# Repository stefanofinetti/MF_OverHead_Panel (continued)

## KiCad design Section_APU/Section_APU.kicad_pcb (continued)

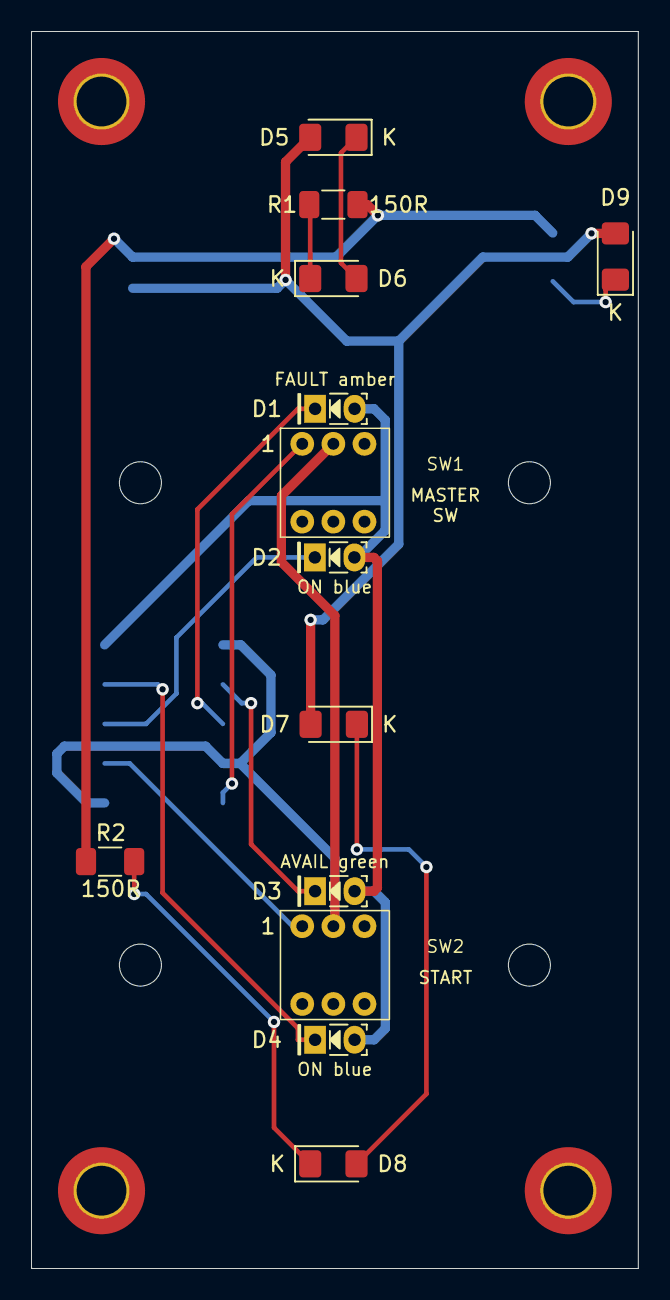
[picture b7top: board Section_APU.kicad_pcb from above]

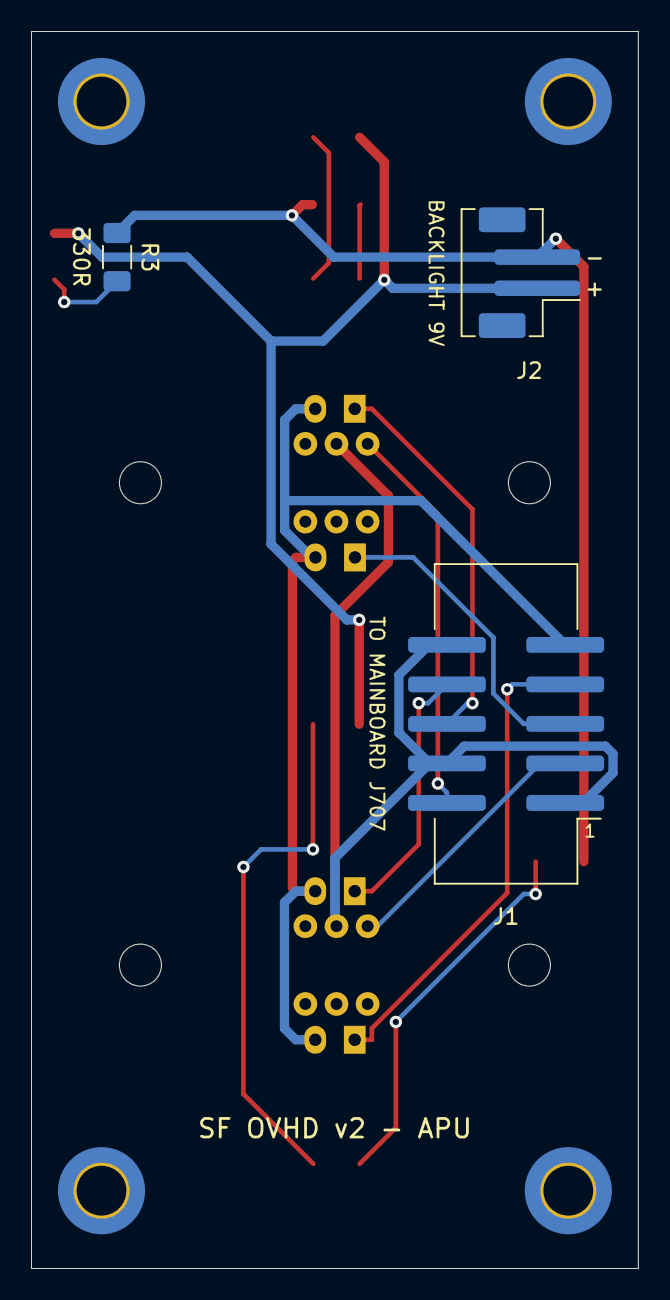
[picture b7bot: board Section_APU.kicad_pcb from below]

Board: 2 copper layers, 39.0 x 79.5 mm, 24 parts (3 on the bottom side), 15 nets.

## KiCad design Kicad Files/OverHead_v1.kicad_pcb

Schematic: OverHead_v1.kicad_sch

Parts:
C1, C2, C3, C4, C7: 100nF; C_1206_3216Metric_Pad1.33x1.80mm_HandSolder
C5: 10uF; C_Elec_4x5.4
C6, C8, C9: 22pF; C_1206_3216Metric_Pad1.33x1.80mm_HandSolder
R1: 10K; R_1206_3216Metric_Pad1.30x1.75mm_HandSolder
U1: ATMega2560; TQFP100-0.5-14X14MM
XT16MHz1: 16MHz; Crystal_SMD_EuroQuartz_MQ-4Pin_7.0x5.0mm_HandSoldering

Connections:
ADR_1_ATT: U1.63 (PJ0); also elsewhere on the board
ADR_1_NAV: U1.64 (PJ1); also elsewhere on the board
ADR_1_OFF: U1.35 (PL0); also elsewhere on the board
ADR_2_ATT: U1.89 (PK0); also elsewhere on the board
ADR_2_NAV: U1.88 (PK1); also elsewhere on the board
ADR_2_OFF: U1.36 (PL1); also elsewhere on the board
ADR_3_ATT: U1.87 (PK2); also elsewhere on the board
ADR_3_NAV: U1.86 (PK3); also elsewhere on the board
ADR_3_OFF: U1.37 (PL2); also elsewhere on the board
ANTI_ICE_ENG1_SW: U1.96 (PF1); also elsewhere on the board
ANTI_ICE_ENG2_SW: U1.95 (PF2); also elsewhere on the board
ANTI_ICE_WING_SW: U1.97 (PF0); also elsewhere on the board
APU_BLEED_SW: U1.90 (PF7); also elsewhere on the board
APU_MASTER_SW: U1.72 (PA6); also elsewhere on the board
APU_START_SW: U1.71 (PA7); also elsewhere on the board
BEACON_ON: U1.58 (PC5); also elsewhere on the board
CLK1: U1.76 (PA2); also elsewhere on the board
CLK2: U1.74 (PA4); also elsewhere on the board
CTR_TK_PUMP_1_SW: U1.17 (PH5); also elsewhere on the board
CTR_TK_PUMP_2_SW: U1.18 (PH6); also elsewhere on the board
DIN1: U1.78 (PA0); also elsewhere on the board
DIN2: U1.75 (PA3); also elsewhere on the board
ELEC_BATT_1_SW: U1.84 (PK5); also elsewhere on the board
ELEC_BATT_2_SW: U1.83 (PK6); also elsewhere on the board
EMERG_OFF: U1.7 (PE5); also elsewhere on the board
EMERG_ON: U1.6 (PE4); also elsewhere on the board
EXT_PWR_SW: U1.70 (PG2); also elsewhere on the board
GND: C1.2, C2.2, C3.2, C4.2, C5.2, C6.2, C7.2, C8.2, C9.2, U1.11 (GND), U1.32 (GND), U1.62 (GND), U1.81 (GND), U1.99 (GND), XT16MHz1.2, XT16MHz1.4; also elsewhere on the board
GND_CTL_SW: U1.82 (PK7); also elsewhere on the board
GPWS_FLAPS3_SW: U1.91 (PF6); also elsewhere on the board
GPWS_GS_SW: U1.92 (PF5); also elsewhere on the board
GPWS_SYS_SW: U1.93 (PF4); also elsewhere on the board
GPWS_TERR_SW: U1.94 (PF3); also elsewhere on the board
LCH1: U1.77 (PA1); also elsewhere on the board
LCH2: U1.73 (PA5); also elsewhere on the board
LT_TK_PUMP_1_SW: U1.12 (PH0); also elsewhere on the board
LT_TK_PUMP_2_SW: U1.13 (PH1); also elsewhere on the board
L_LDG_LIGHT_ON: U1.23 (PB4); also elsewhere on the board
L_LDG_LIGHT_RETR: U1.24 (PB5); also elsewhere on the board
MISO: U1.22 (PB3); also elsewhere on the board
MOSI: U1.21 (PB2); also elsewhere on the board
NAV_1: U1.56 (PC3); also elsewhere on the board
NAV_1_OFF: U1.55 (PC2); also elsewhere on the board
NOSE_OFF: U1.54 (PC1); also elsewhere on the board
NOSE_TO: U1.53 (PC0); also elsewhere on the board
NOSMOKING_ON: U1.50 (PD7); also elsewhere on the board
unnamed: C7.1, U1.98 (AREF)
unnamed: C9.1, U1.34 (XTAL1), XT16MHz1.1
unnamed: C8.1, U1.33 (XTAL2), XT16MHz1.3
OXY_CREW_SUPPLY_SW: U1.85 (PK4); also elsewhere on the board
PACK1_SW: U1.51 (PG0); also elsewhere on the board
PACK2_SW: U1.52 (PG1); also elsewhere on the board
RESET: C6.1, R1.2, U1.30 (~RESET); also elsewhere on the board
RT_TK_PUMP_1_SW: U1.15 (PH3); also elsewhere on the board
RT_TK_PUMP_2_SW: U1.16 (PH4); also elsewhere on the board
RWY_TURN_ON: U1.60 (PC7); also elsewhere on the board
RXD: U1.2 (PE0); also elsewhere on the board
R_LDG_LIGHT_ON: U1.25 (PB6); also elsewhere on the board
R_LDG_LIGHT_RETR: U1.26 (PB7); also elsewhere on the board
SCK: U1.20 (PB1); also elsewhere on the board
SCL: U1.43 (PD0); also elsewhere on the board
SDA: U1.44 (PD1); also elsewhere on the board
SEATBELTS_ON: U1.45 (PD2); also elsewhere on the board
STROBE_ON: U1.59 (PC6); also elsewhere on the board
TXD: U1.3 (PE1); also elsewhere on the board
VIN: C1.1, C2.1, C3.1, C4.1, C5.1, R1.1, U1.10 (VCC), U1.31 (VCC), U1.61 (VCC), U1.80 (VCC), U1.100 (AVCC); also elsewhere on the board
WING_ON: U1.57 (PC4); also elsewhere on the board
XFEED_SW: U1.1 (PG5); also elsewhere on the board

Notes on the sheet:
DM13A Drivers

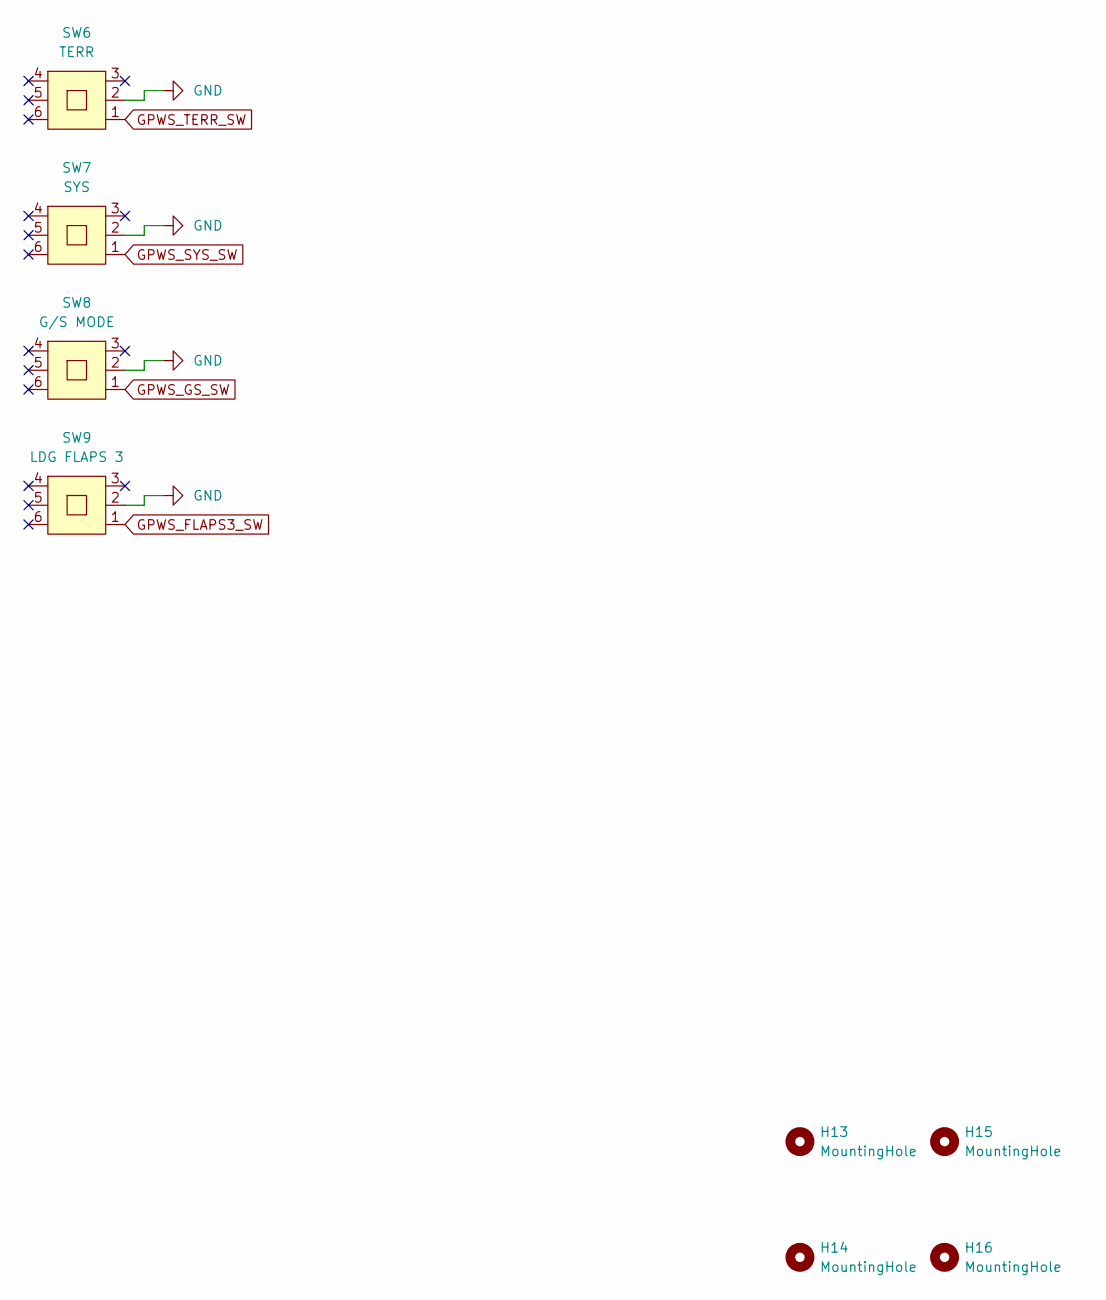
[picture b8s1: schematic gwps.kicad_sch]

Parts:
H13, H14, H15, H16: MountingHole; MountingHole_3.2mm_M3_DIN965_Pad_TopBottom
SW6: TERR; G-Switch PS-7054DVB-6PN
SW7: SYS; G-Switch PS-7054DVB-6PN
SW8: G/S MODE; G-Switch PS-7054DVB-6PN
SW9: LDG FLAPS 3; G-Switch PS-7054DVB-6PN

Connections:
GND: SW6.2, SW7.2, SW8.2, SW9.2; also elsewhere on the board
GPWS_FLAPS3_SW: SW9.1; also elsewhere on the board
GPWS_GS_SW: SW8.1; also elsewhere on the board
GPWS_SYS_SW: SW7.1; also elsewhere on the board
GPWS_TERR_SW: SW6.1; also elsewhere on the board

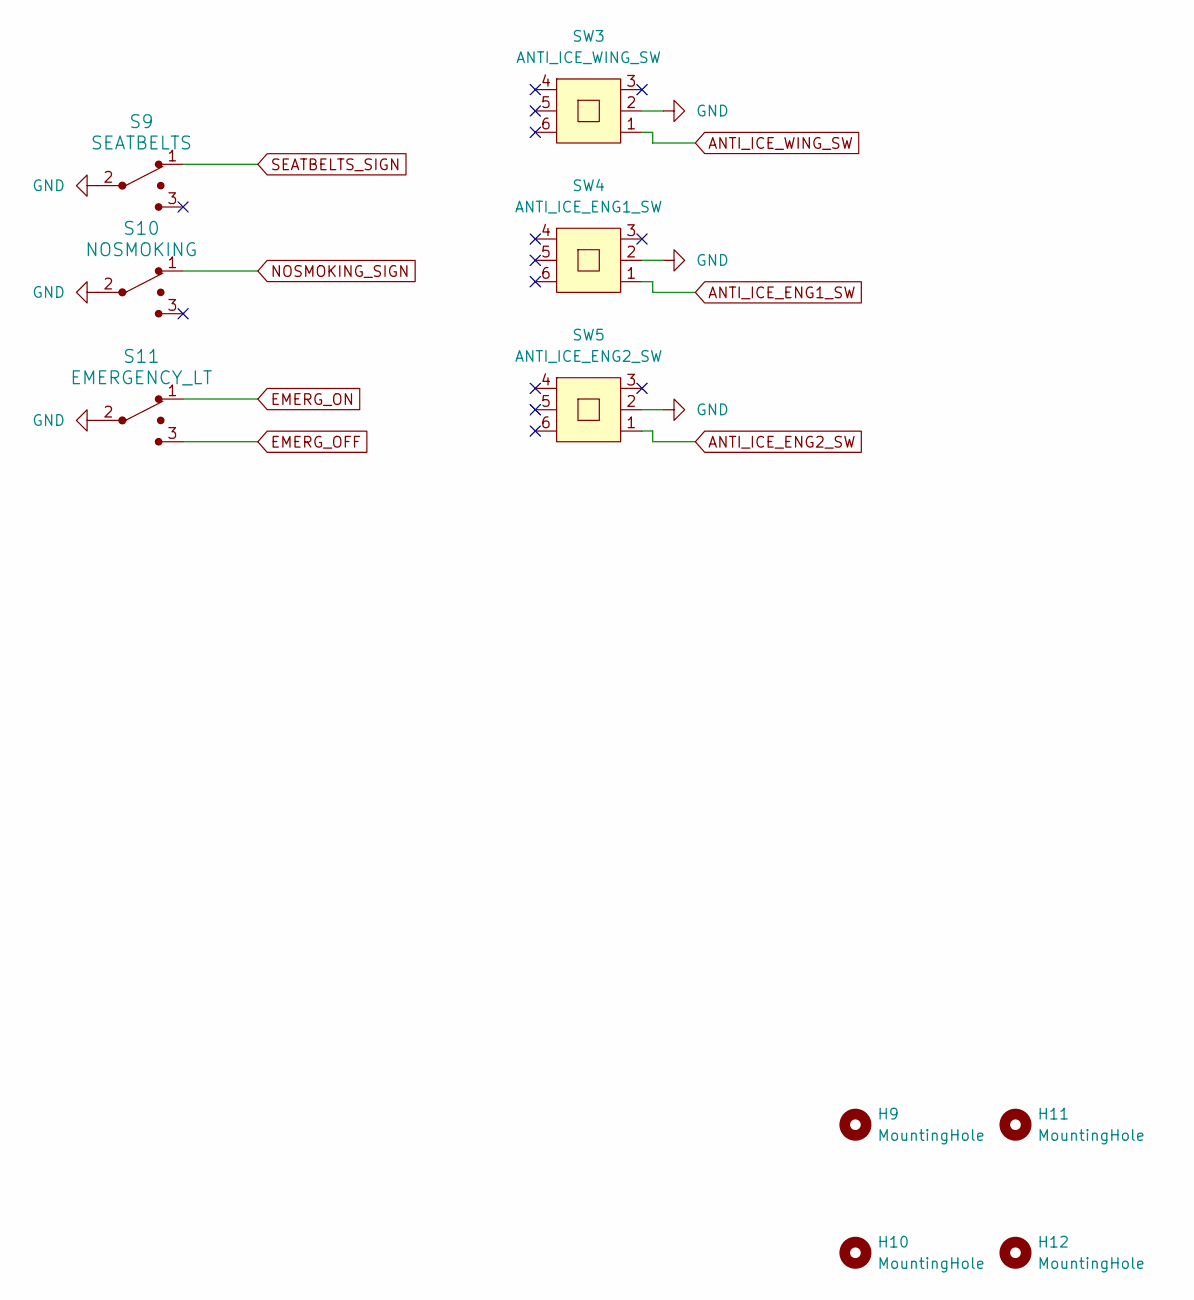
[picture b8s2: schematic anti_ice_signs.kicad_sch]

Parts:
H9, H10, H11, H12: MountingHole; MountingHole_3.2mm_M3_DIN965_Pad_TopBottom
S9: SEATBELTS; Toggle_Switch_100SP1T1B4M2QE; MPN 100SP1T1B4M2QE; Digi-Key_PN EG2355-ND
S10: NOSMOKING; Toggle_Switch_100SP1T1B4M2QE; MPN 100SP1T1B4M2QE; Digi-Key_PN EG2355-ND
S11: EMERGENCY_LT; Toggle_Switch_100SP1T1B4M2QE; MPN 100SP1T1B4M2QE; Digi-Key_PN EG2355-ND
SW3: ANTI_ICE_WING_SW; G-Switch PS-7054DVB-6PN
SW4: ANTI_ICE_ENG1_SW; G-Switch PS-7054DVB-6PN
SW5: ANTI_ICE_ENG2_SW; G-Switch PS-7054DVB-6PN

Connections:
ANTI_ICE_ENG1_SW: SW4.1; also elsewhere on the board
ANTI_ICE_ENG2_SW: SW5.1; also elsewhere on the board
ANTI_ICE_WING_SW: SW3.1; also elsewhere on the board
EMERG_OFF: S11.3; also elsewhere on the board
EMERG_ON: S11.1; also elsewhere on the board
GND: S9.2 (Com), S10.2 (Com), S11.2 (Com), SW3.2, SW4.2, SW5.2; also elsewhere on the board
NOSMOKING_OFF: S10.3
NOSMOKING_ON: S10.1; also elsewhere on the board
SEATBELTS_OFF: S9.3
SEATBELTS_ON: S9.1; also elsewhere on the board

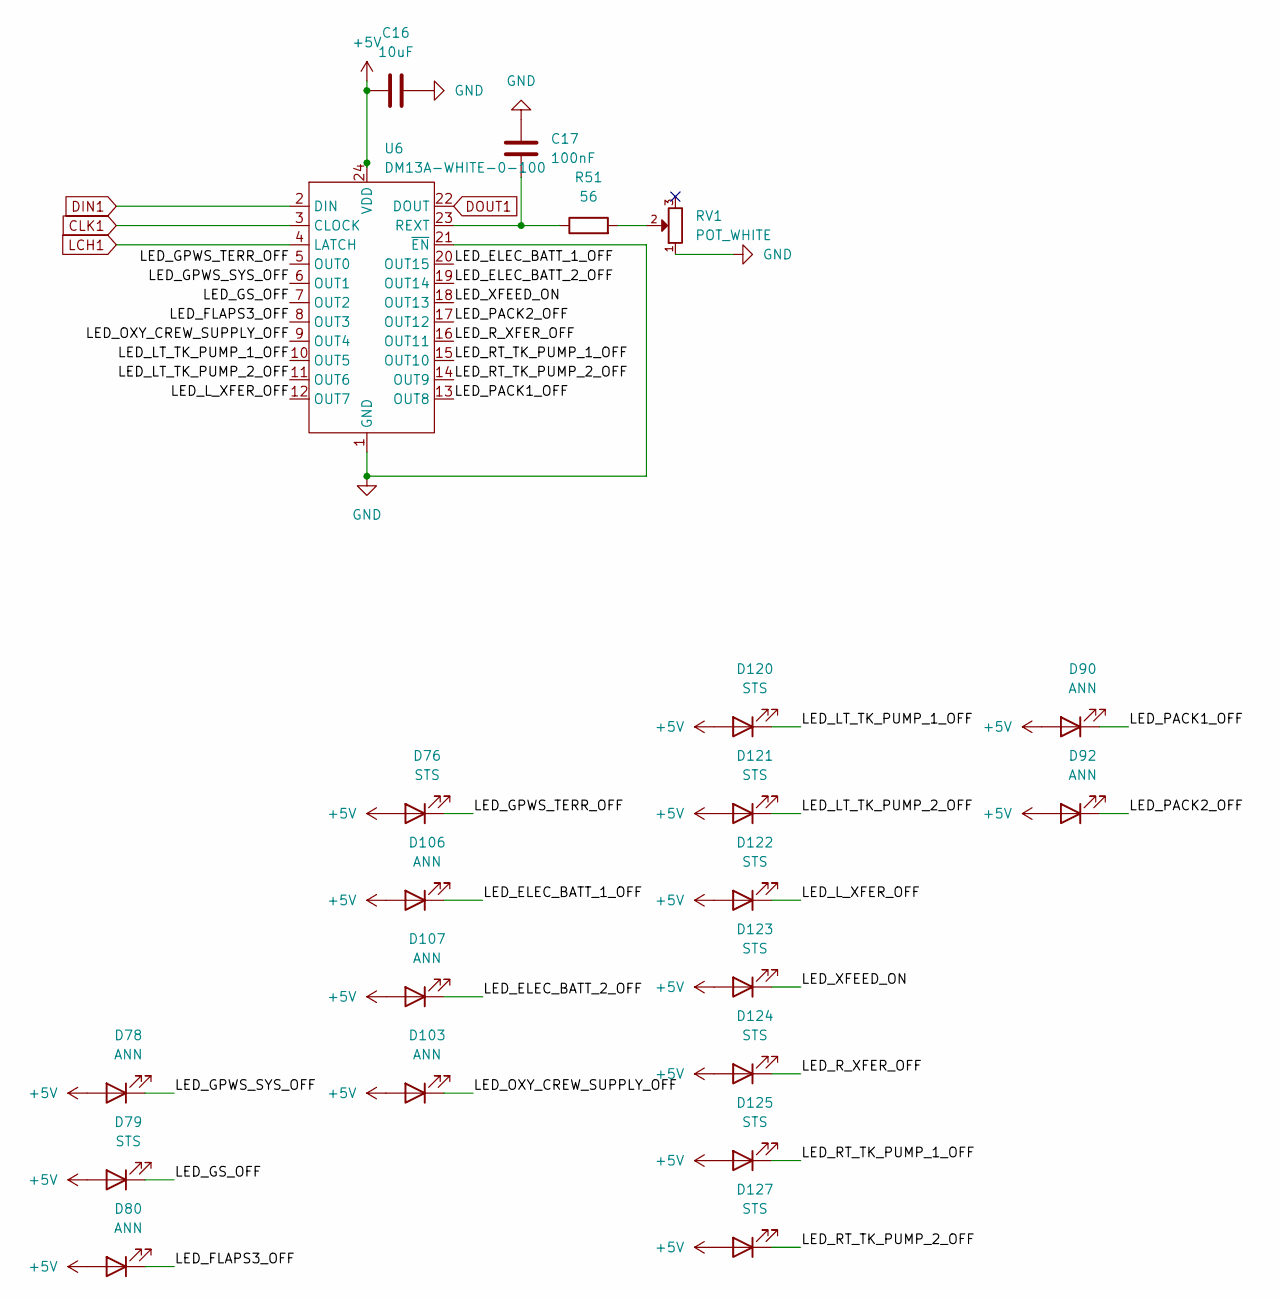
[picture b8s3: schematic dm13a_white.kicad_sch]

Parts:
C16: 10uF; C_1206_3216Metric_Pad1.33x1.80mm_HandSolder
C17: 100nF; C_1206_3216Metric_Pad1.33x1.80mm_HandSolder
D76, D79, D120, D121, D122, D123, D124, D125, D127: STS; LED_Rectangular_W3.9mm_H1.8mm_FlatTop
D78, D80, D90, D92, D103, D106, D107: ANN; LED_Rectangular_W3.9mm_H1.8mm_FlatTop
R51: 56; R_1206_3216Metric_Pad1.30x1.75mm_HandSolder
RV1: POT_WHITE; potentiometer_3362P
U6: DM13A-WHITE-0-100; SOP-24_7.5x15.4mm_P1.27mm

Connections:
+5V: C16.1, D76.2 (A), D78.2 (A), D79.2 (A), D80.2 (A), D90.2 (A), D92.2 (A), D103.2 (A), D106.2 (A), D107.2 (A), D120.2 (A), D121.2 (A), D122.2 (A), D123.2 (A), D124.2 (A), D125.2 (A), D127.2 (A), U6.24 (VDD); also elsewhere on the board
/DM13-WHITE/LED_ELEC_BATT_1_OFF: D106.1 (K), U6.20 (OUT15)
/DM13-WHITE/LED_ELEC_BATT_2_OFF: D107.1 (K), U6.19 (OUT14)
/DM13-WHITE/LED_FLAPS3_OFF: D80.1 (K), U6.8 (OUT3)
/DM13-WHITE/LED_GPWS_SYS_OFF: D78.1 (K), U6.6 (OUT1)
/DM13-WHITE/LED_GPWS_TERR_OFF: D76.1 (K), U6.5 (OUT0)
/DM13-WHITE/LED_GS_OFF: D79.1 (K), U6.7 (OUT2)
/DM13-WHITE/LED_LT_TK_PUMP_1_OFF: D120.1 (K), U6.10 (OUT5)
/DM13-WHITE/LED_LT_TK_PUMP_2_OFF: D121.1 (K), U6.11 (OUT6)
/DM13-WHITE/LED_L_XFER_OFF: D122.1 (K), U6.12 (OUT7)
/DM13-WHITE/LED_OXY_CREW_SUPPLY_OFF: D103.1 (K), U6.9 (OUT4)
/DM13-WHITE/LED_PACK1_OFF: D90.1 (K), U6.13 (OUT8)
/DM13-WHITE/LED_PACK2_OFF: D92.1 (K), U6.17 (OUT12)
/DM13-WHITE/LED_RT_TK_PUMP_1_OFF: D125.1 (K), U6.15 (OUT10)
/DM13-WHITE/LED_RT_TK_PUMP_2_OFF: D127.1 (K), U6.14 (OUT9)
/DM13-WHITE/LED_R_XFER_OFF: D124.1 (K), U6.16 (OUT11)
/DM13-WHITE/LED_XFEED_ON: D123.1 (K), U6.18 (OUT13)
CLK1: U6.3 (CLOCK); also elsewhere on the board
DIN1: U6.2 (DIN); also elsewhere on the board
DOUT1: U6.22 (DOUT); also elsewhere on the board
GND: C16.2, C17.1, RV1.1, U6.1 (GND), U6.21 (~EN); also elsewhere on the board
LCH1: U6.4 (LATCH); also elsewhere on the board
unnamed: R51.2, RV1.2
unnamed: C17.2, R51.1, U6.23 (REXT)

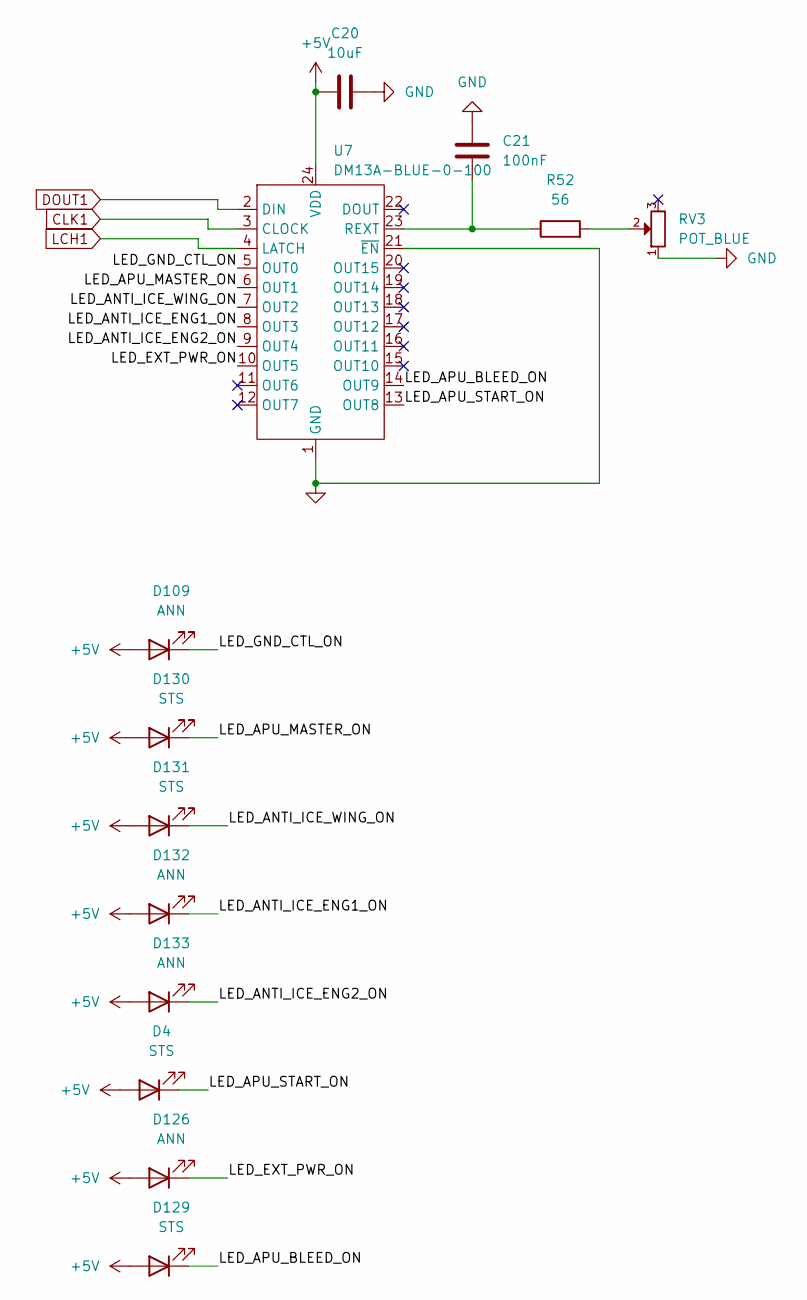
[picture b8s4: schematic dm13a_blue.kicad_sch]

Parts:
C20: 10uF; C_1206_3216Metric_Pad1.33x1.80mm_HandSolder
C21: 100nF; C_1206_3216Metric_Pad1.33x1.80mm_HandSolder
D4, D129, D130, D131: STS; LED_Rectangular_W3.9mm_H1.8mm_FlatTop
D109, D126, D132, D133: ANN; LED_Rectangular_W3.9mm_H1.8mm_FlatTop
R52: 56; R_1206_3216Metric_Pad1.30x1.75mm_HandSolder
RV3: POT_BLUE; potentiometer_3362P
U7: DM13A-BLUE-0-100; SOP-24_7.5x15.4mm_P1.27mm

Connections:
+5V: C20.1, D4.2 (A), D109.2 (A), D126.2 (A), D129.2 (A), D130.2 (A), D131.2 (A), D132.2 (A), D133.2 (A), U7.24 (VDD); also elsewhere on the board
/DM13-BLUE/LED_ANTI_ICE_ENG1_ON: D132.1 (K), U7.8 (OUT3)
/DM13-BLUE/LED_ANTI_ICE_ENG2_ON: D133.1 (K), U7.9 (OUT4)
/DM13-BLUE/LED_ANTI_ICE_WING_ON: D131.1 (K), U7.7 (OUT2)
/DM13-BLUE/LED_APU_BLEED_ON: D129.1 (K), U7.14 (OUT9)
/DM13-BLUE/LED_APU_MASTER_ON: D130.1 (K), U7.6 (OUT1)
/DM13-BLUE/LED_APU_START_ON: D4.1 (K), U7.13 (OUT8)
/DM13-BLUE/LED_EXT_PWR_ON: D126.1 (K), U7.10 (OUT5)
/DM13-BLUE/LED_GND_CTL_ON: D109.1 (K), U7.5 (OUT0)
CLK1: U7.3 (CLOCK); also elsewhere on the board
DOUT1: U7.2 (DIN); also elsewhere on the board
GND: C20.2, C21.1, RV3.1, U7.1 (GND), U7.21 (~EN); also elsewhere on the board
LCH1: U7.4 (LATCH); also elsewhere on the board
unnamed: R52.2, RV3.2
unnamed: C21.2, R52.1, U7.23 (REXT)

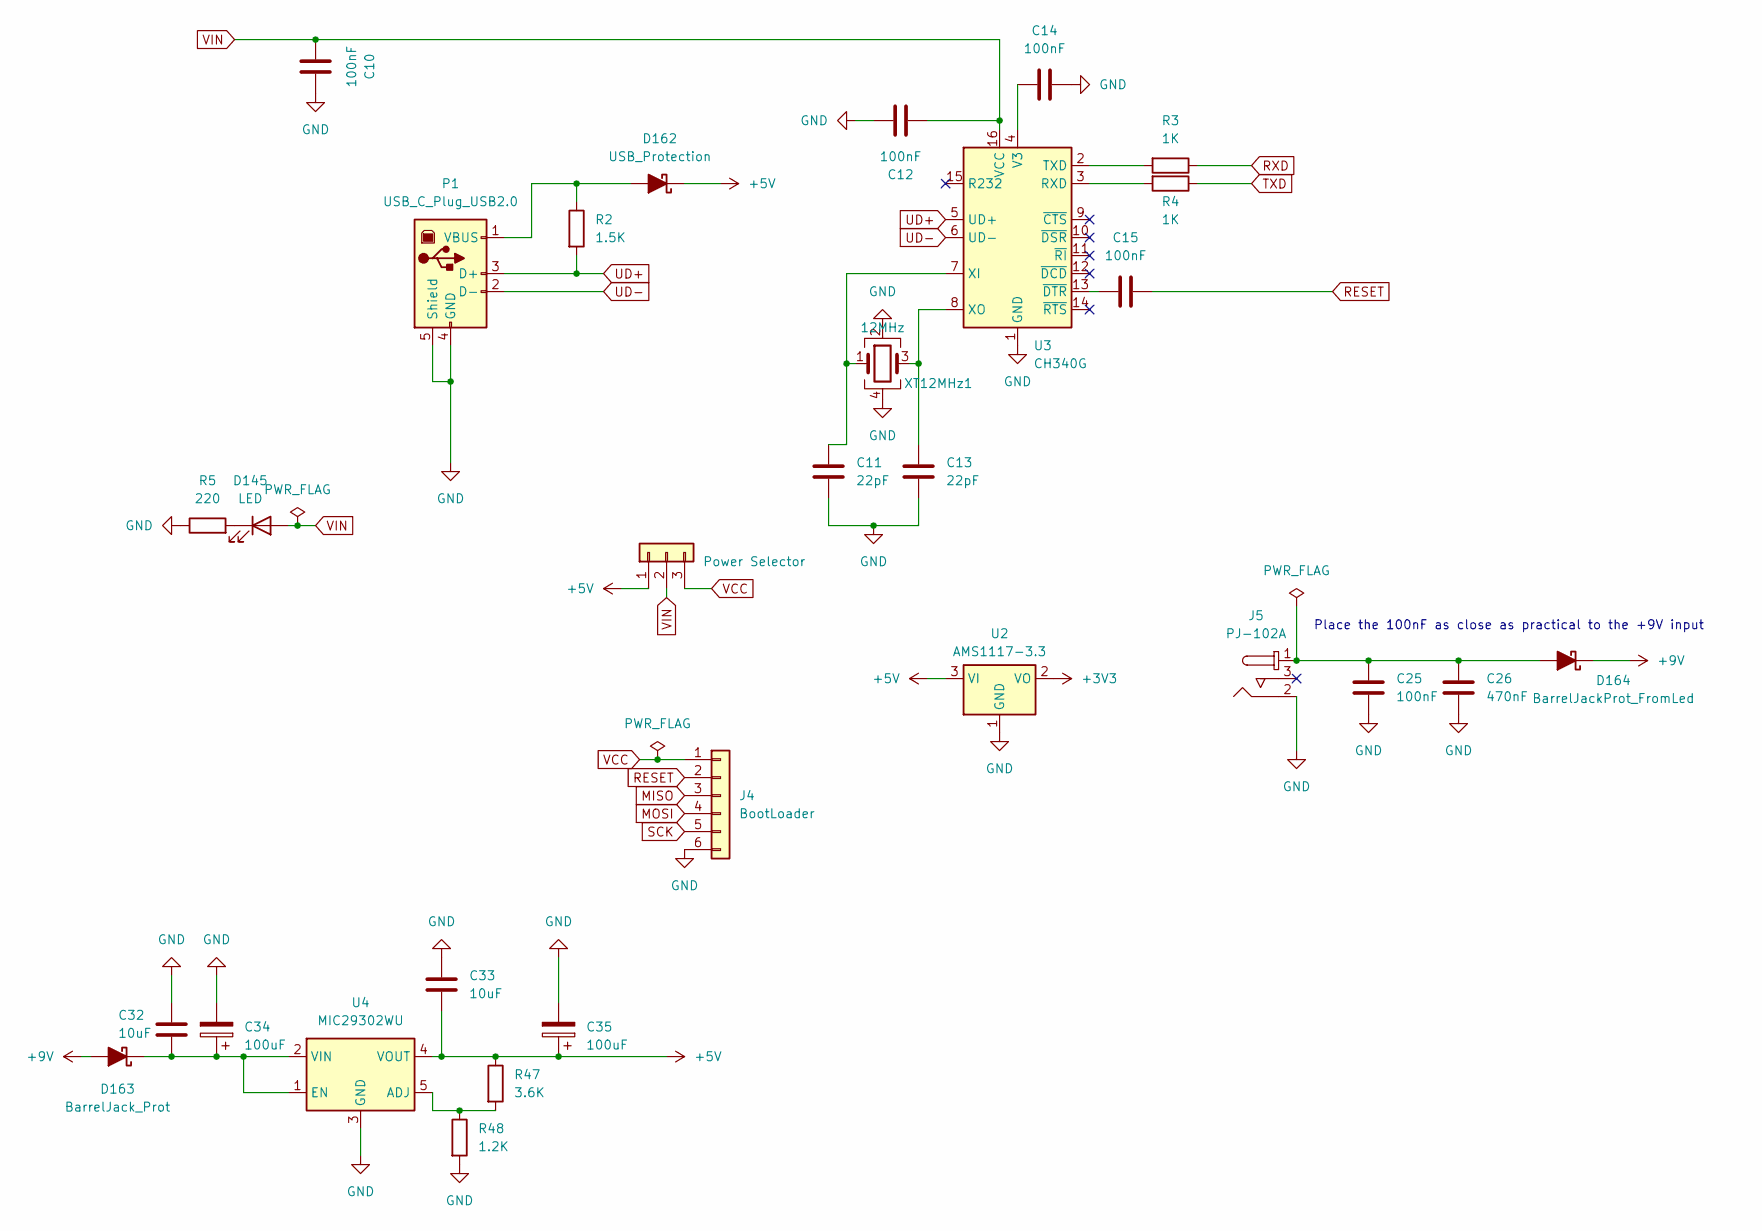
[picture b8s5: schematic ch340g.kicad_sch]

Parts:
C10, C12, C14, C15, C25: 100nF; C_1206_3216Metric_Pad1.33x1.80mm_HandSolder
C11, C13: 22pF; C_1206_3216Metric_Pad1.33x1.80mm_HandSolder
C26: 470nF; C_1206_3216Metric_Pad1.33x1.80mm_HandSolder
C32, C33: 10uF; C_1206_3216Metric_Pad1.33x1.80mm_HandSolder
C34, C35: 100uF; C_Elec_6.3x7.7
D145: LED; LED_1206_3216Metric_Pad1.42x1.75mm_HandSolder
D162: USB_Protection; D_SMA_DO-214-AC
D163: BarrelJack_Prot; D_SMA_DO-214-AC
D164: BarrelJackProt_FromLed; D_SMA_DO-214-AC
J4: BootLoader; PinHeader_1x06_P2.54mm_Vertical
J5: PJ-102A; Barrel_Jack_5.5mmODx2.1mmID_PJ-102A; MPN PJ-102A; Digi-Key_PN CP-102A-ND
JP1: Power Selector; PinHeader_1x03_P2.54mm_Vertical
P1: USB_C_Plug_USB2.0; USB_B_OST_USB-B1HSxx_Horizontal
R2: 1.5K; R_1206_3216Metric_Pad1.30x1.75mm_HandSolder
R3, R4: 1K; R_1206_3216Metric_Pad1.30x1.75mm_HandSolder
R5: 220; R_1206_3216Metric_Pad1.30x1.75mm_HandSolder
R47: 3.6K; R_1206_3216Metric_Pad1.30x1.75mm_HandSolder
R48: 1.2K; R_1206_3216Metric_Pad1.30x1.75mm_HandSolder
U2: AMS1117-3.3; SOT-223-3_TabPin2
U3: CH340G; SOIC-16_3.9x9.9mm_P1.27mm
U4: MIC29302WU; TO-263-5_TabPin3
XT12MHz1: 12MHz; Crystal_SMD_EuroQuartz_MQ-4Pin_7.0x5.0mm_HandSoldering

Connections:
+3V3: U2.2 (VO); also elsewhere on the board
+5V: C33.2, C35.1, D162.1 (K), JP1.1, R47.1, U2.3 (VI), U4.4 (VOUT); also elsewhere on the board
+9V: D163.2 (A), D164.1 (K); also elsewhere on the board
GND: C10.2, C11.1, C12.2, C13.1, C14.2, C25.2, C26.2, C32.1, C33.1, C34.2, C35.2, J4.6, J5.2, P1.4 (GND), P1.5 (Shield), R5.1, R48.2, U2.1 (GND), U3.1 (GND), U4.3 (GND), XT12MHz1.2, XT12MHz1.4; also elsewhere on the board
MISO: J4.3; also elsewhere on the board
MOSI: J4.4; also elsewhere on the board
unnamed: D145.1 (K), R5.2
unnamed: D162.2 (A), P1.1 (VBUS), R2.1
unnamed: C32.2, C34.1, D163.1 (K), U4.1 (EN), U4.2 (VIN)
unnamed: C25.1, C26.1, D164.2 (A), J5.1
unnamed: R4.2, U3.3 (RXD)
unnamed: R3.2, U3.2 (TXD)
unnamed: C14.1, U3.4 (V3)
unnamed: C11.2, U3.7 (XI), XT12MHz1.1
unnamed: C13.2, U3.8 (XO), XT12MHz1.3
unnamed: C15.1, U3.13 (~DTR)
unnamed: R47.2, R48.1, U4.5 (ADJ)
RESET: C15.2, J4.2; also elsewhere on the board
RXD: R3.1; also elsewhere on the board
SCK: J4.5; also elsewhere on the board
TXD: R4.1; also elsewhere on the board
UD+: P1.3 (D+), R2.2, U3.5 (UD+)
UD-: P1.2 (D-), U3.6 (UD-)
VCC: J4.1, JP1.3
VIN: C10.1, C12.1, D145.2 (A), JP1.2, U3.16 (VCC); also elsewhere on the board

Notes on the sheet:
Place the 100nF as close as practical to the +9V input

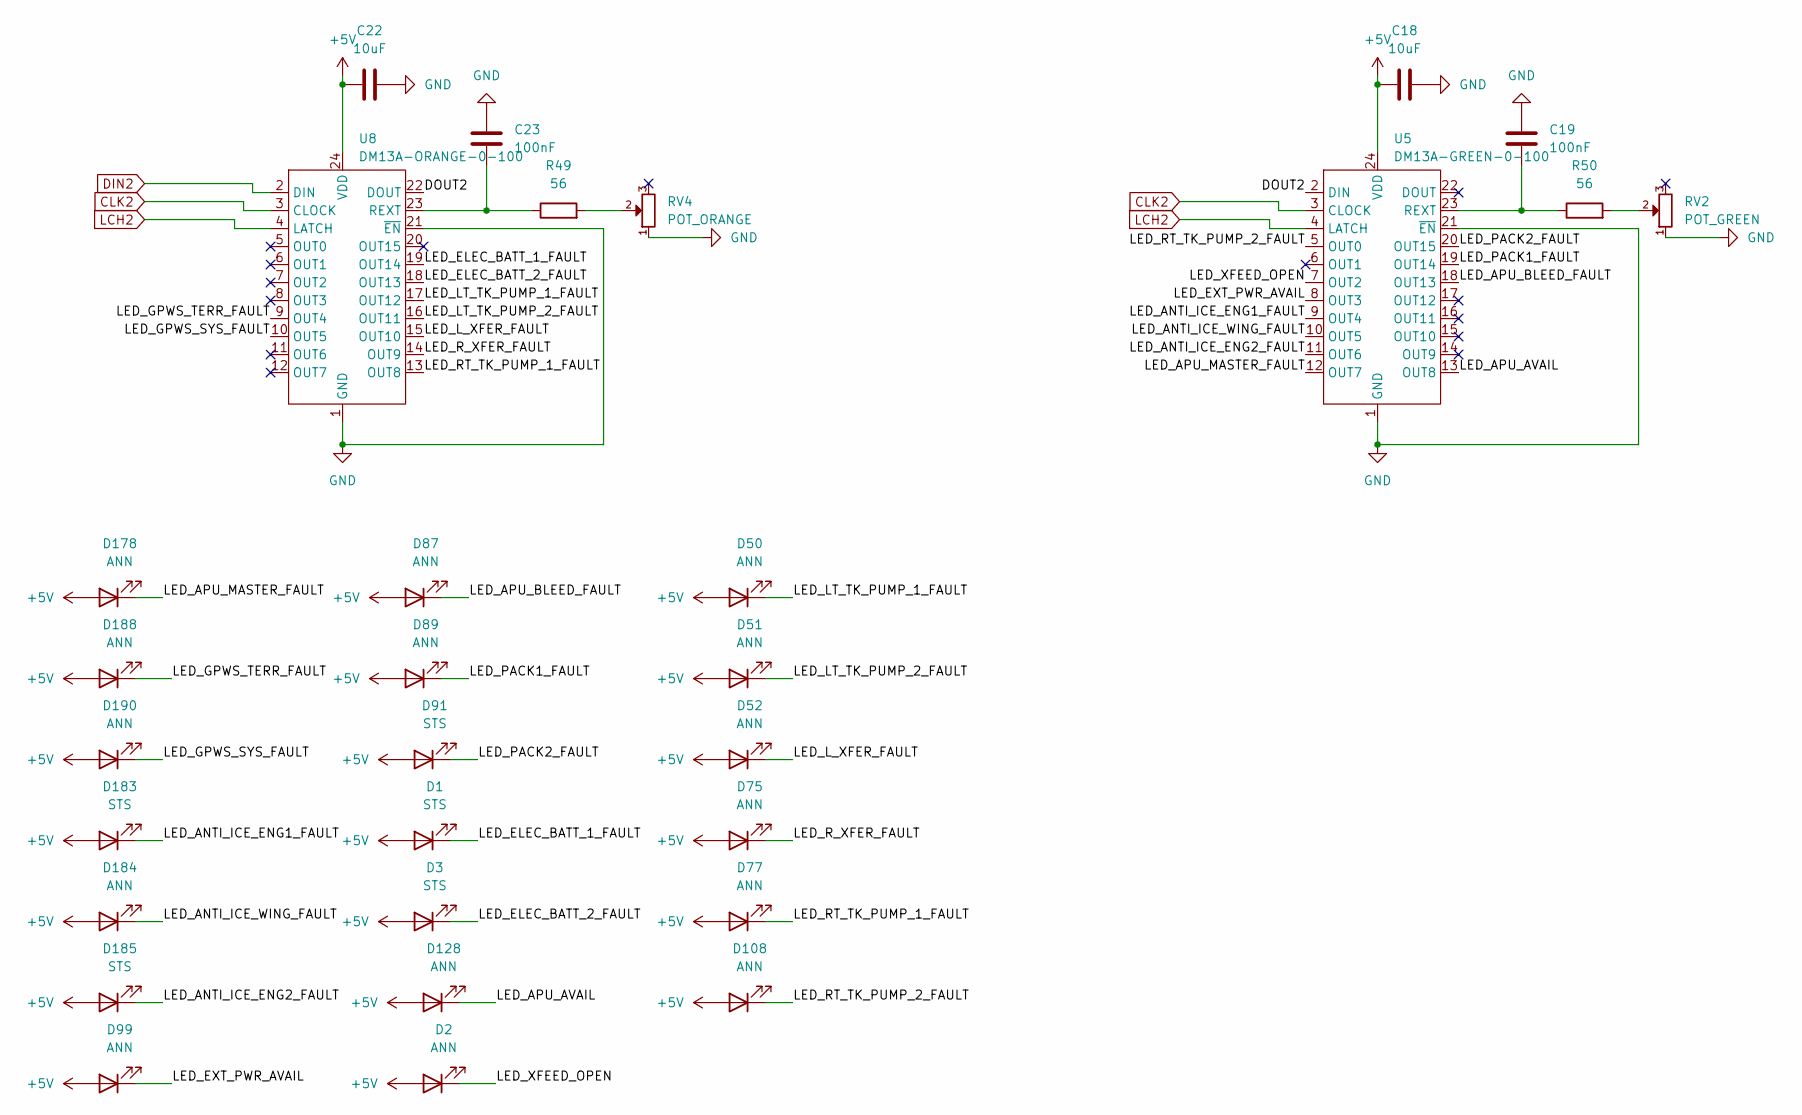
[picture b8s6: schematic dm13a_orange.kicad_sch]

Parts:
C18, C22: 10uF; C_1206_3216Metric_Pad1.33x1.80mm_HandSolder
C19, C23: 100nF; C_1206_3216Metric_Pad1.33x1.80mm_HandSolder
D1, D3, D91, D183, D185: STS; LED_Rectangular_W3.9mm_H1.8mm_FlatTop
D2, D50, D51, D52, D75, D77, D87, D89, D99, D108, D128, D178, D184, D188, D190: ANN; LED_Rectangular_W3.9mm_H1.8mm_FlatTop
R49, R50: 56; R_1206_3216Metric_Pad1.30x1.75mm_HandSolder
RV2: POT_GREEN; potentiometer_3362P
RV4: POT_ORANGE; potentiometer_3362P
U5: DM13A-GREEN-0-100; SOP-24_7.5x15.4mm_P1.27mm
U8: DM13A-ORANGE-0-100; SOP-24_7.5x15.4mm_P1.27mm

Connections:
+5V: C18.1, C22.1, D1.2 (A), D2.2 (A), D3.2 (A), D50.2 (A), D51.2 (A), D52.2 (A), D75.2 (A), D77.2 (A), D87.2 (A), D89.2 (A), D91.2 (A), D99.2 (A), D108.2 (A), D128.2 (A), D178.2 (A), D183.2 (A), D184.2 (A), D185.2 (A), D188.2 (A), D190.2 (A), U5.24 (VDD), U8.24 (VDD); also elsewhere on the board
/DM13-ORANGE/DOUT2: U5.2 (DIN), U8.22 (DOUT)
/DM13-ORANGE/LED_ANTI_ICE_ENG1_FAULT: D183.1 (K), U5.9 (OUT4)
/DM13-ORANGE/LED_ANTI_ICE_ENG2_FAULT: D185.1 (K), U5.11 (OUT6)
/DM13-ORANGE/LED_ANTI_ICE_WING_FAULT: D184.1 (K), U5.10 (OUT5)
/DM13-ORANGE/LED_APU_AVAIL: D128.1 (K), U5.13 (OUT8)
/DM13-ORANGE/LED_APU_BLEED_FAULT: D87.1 (K), U5.18 (OUT13)
/DM13-ORANGE/LED_APU_MASTER_FAULT: D178.1 (K), U5.12 (OUT7)
/DM13-ORANGE/LED_ELEC_BATT_1_FAULT: D1.1 (K), U8.19 (OUT14)
/DM13-ORANGE/LED_ELEC_BATT_2_FAULT: D3.1 (K), U8.18 (OUT13)
/DM13-ORANGE/LED_EXT_PWR_AVAIL: D99.1 (K), U5.8 (OUT3)
/DM13-ORANGE/LED_GPWS_SYS_FAULT: D190.1 (K), U8.10 (OUT5)
/DM13-ORANGE/LED_GPWS_TERR_FAULT: D188.1 (K), U8.9 (OUT4)
/DM13-ORANGE/LED_LT_TK_PUMP_1_FAULT: D50.1 (K), U8.17 (OUT12)
/DM13-ORANGE/LED_LT_TK_PUMP_2_FAULT: D51.1 (K), U8.16 (OUT11)
/DM13-ORANGE/LED_L_XFER_FAULT: D52.1 (K), U8.15 (OUT10)
/DM13-ORANGE/LED_PACK1_FAULT: D89.1 (K), U5.19 (OUT14)
/DM13-ORANGE/LED_PACK2_FAULT: D91.1 (K), U5.20 (OUT15)
/DM13-ORANGE/LED_RT_TK_PUMP_1_FAULT: D77.1 (K), U8.13 (OUT8)
/DM13-ORANGE/LED_RT_TK_PUMP_2_FAULT: D108.1 (K), U5.5 (OUT0)
/DM13-ORANGE/LED_R_XFER_FAULT: D75.1 (K), U8.14 (OUT9)
/DM13-ORANGE/LED_XFEED_OPEN: D2.1 (K), U5.7 (OUT2)
CLK2: U5.3 (CLOCK), U8.3 (CLOCK); also elsewhere on the board
DIN2: U8.2 (DIN); also elsewhere on the board
GND: C18.2, C19.1, C22.2, C23.1, RV2.1, RV4.1, U5.1 (GND), U5.21 (~EN), U8.1 (GND), U8.21 (~EN); also elsewhere on the board
LCH2: U5.4 (LATCH), U8.4 (LATCH); also elsewhere on the board
unnamed: R49.2, RV4.2
unnamed: R50.2, RV2.2
unnamed: C19.2, R50.1, U5.23 (REXT)
unnamed: C23.2, R49.1, U8.23 (REXT)

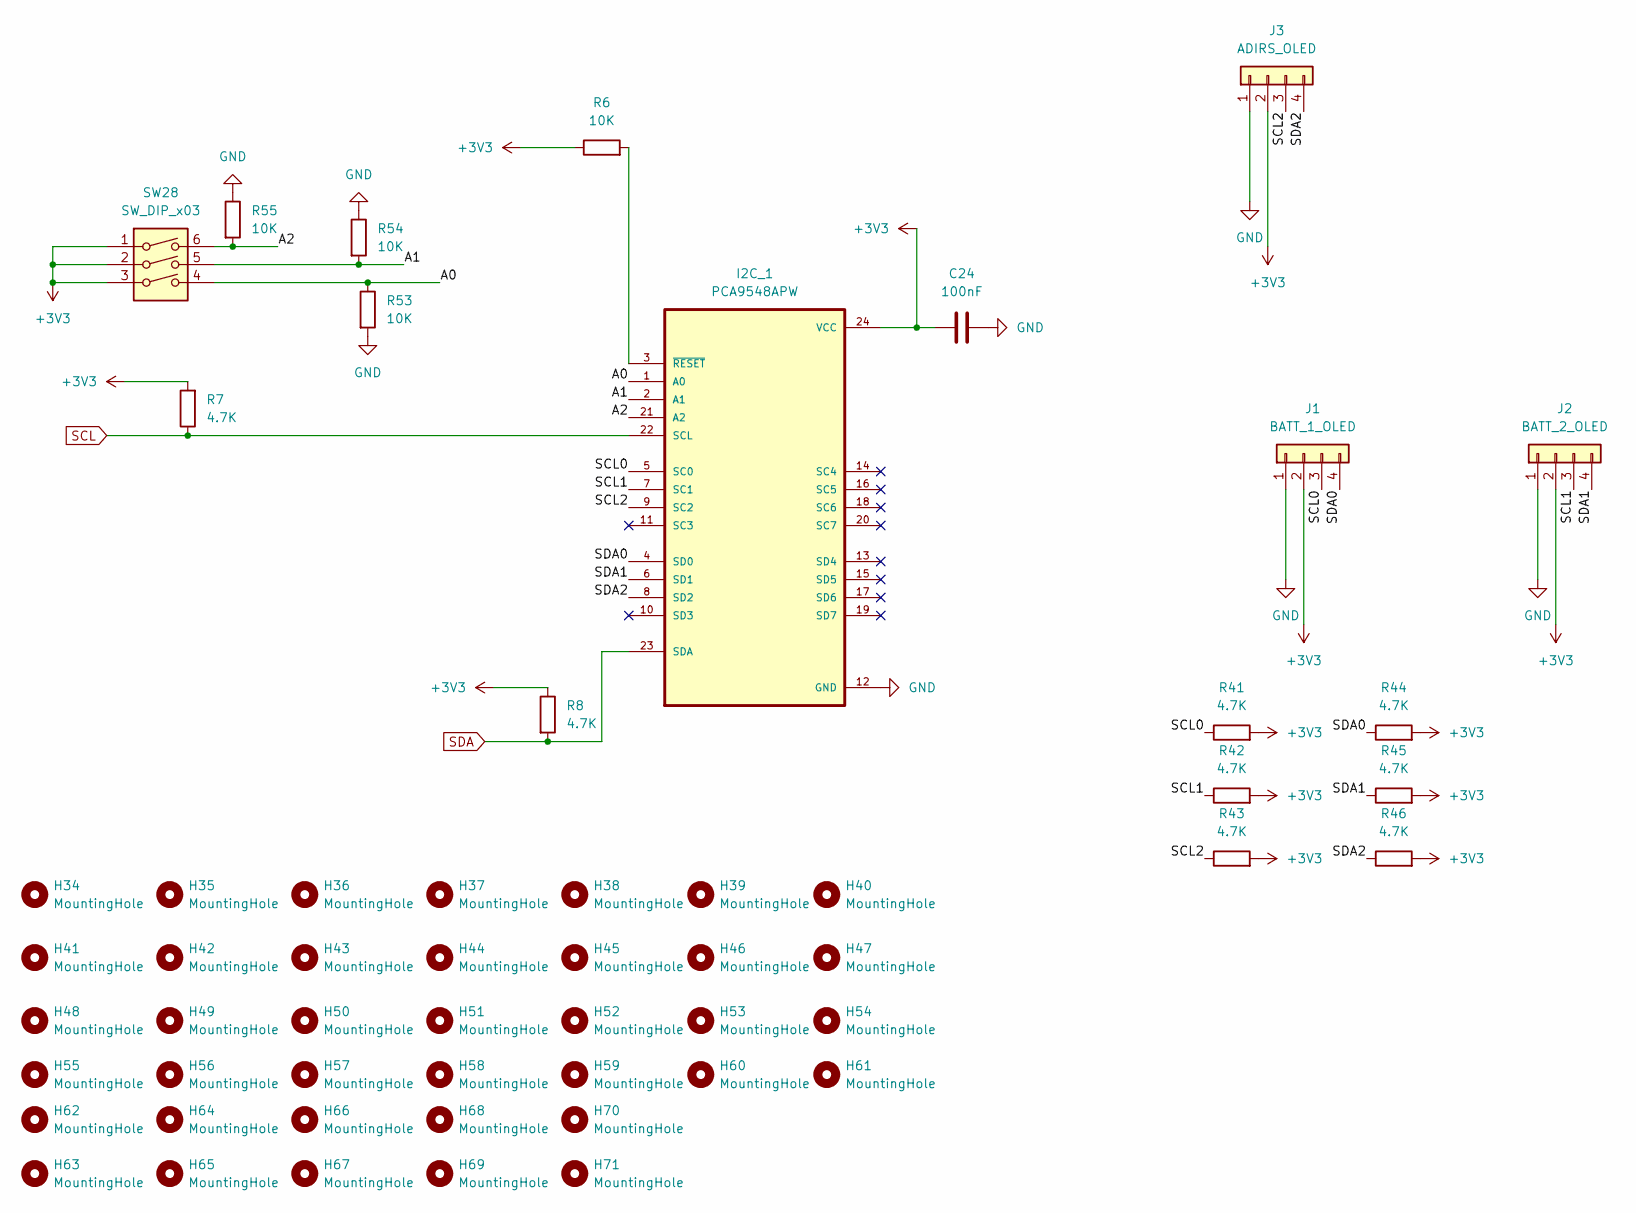
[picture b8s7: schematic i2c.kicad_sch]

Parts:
C24: 100nF; C_1206_3216Metric_Pad1.33x1.80mm_HandSolder
H34, H35, H36, H37, H38, H39, H40, H41, H42, H43, H44, H45, H46, H47, H48, H49, H50, H51, H52, H53, H54, H55, H56, H57, H58, H59, H60, H61, H62, H63, H64, H65, H66, H67, H68, H69, H70, H71: MountingHole; MountingHole_2.7mm_M2.5
I2C_1: PCA9548APW; SOP65P640X120-24N
J1: BATT_1_OLED; PinSocket_1x04_P2.54mm_Vertical
J2: BATT_2_OLED; PinSocket_1x04_P2.54mm_Vertical
J3: ADIRS_OLED; PinSocket_1x04_P2.54mm_Vertical
R6, R53, R54, R55: 10K; R_1206_3216Metric_Pad1.30x1.75mm_HandSolder
R7, R8, R41, R42, R43, R44, R45, R46: 4.7K; R_1206_3216Metric_Pad1.30x1.75mm_HandSolder
SW28: SW_DIP_x03; SW_DIP_SPSTx03_Slide_9.78x9.8mm_W7.62mm_P2.54mm

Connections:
+3V3: C24.1, I2C_1.24 (VCC), J1.2, J2.2, J3.2, R6.1, R7.2, R8.1, R41.2, R42.2, R43.2, R44.2, R45.2, R46.2, SW28.1, SW28.2, SW28.3; also elsewhere on the board
/I2C/A0: I2C_1.1 (A0), R53.1, SW28.4
/I2C/A1: I2C_1.2 (A1), R54.2, SW28.5
/I2C/A2: I2C_1.21 (A2), R55.2, SW28.6
/I2C/SCL0: I2C_1.5 (SC0), J1.3, R41.1
/I2C/SCL1: I2C_1.7 (SC1), J2.3, R42.1
/I2C/SCL2: I2C_1.9 (SC2), J3.3, R43.1
/I2C/SDA0: I2C_1.4 (SD0), J1.4, R44.1
/I2C/SDA1: I2C_1.6 (SD1), J2.4, R45.1
/I2C/SDA2: I2C_1.8 (SD2), J3.4, R46.1
GND: C24.2, I2C_1.12 (GND), J1.1, J2.1, J3.1, R53.2, R54.1, R55.1; also elsewhere on the board
unnamed: I2C_1.3 (~RESET), R6.2
SCL: I2C_1.22 (SCL), R7.1; also elsewhere on the board
SDA: I2C_1.23 (SDA), R8.2; also elsewhere on the board
